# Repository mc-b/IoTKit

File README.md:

Internet der Dinge Kit
----------------------

| IoTKit V1   | IoTKit V2  | IoTKit V3  |
|  :-------:  | :-------:  | :-------:  |
||||
|[Dokumentation](https://github.com/mc-b/IoTKitV1)|[Dokumentation](https://github.com/mc-b/IoTKitV2)|[Dokumentation](https://github.com/mc-b/IoTKitV3)|

### Kurse:

Internet of Things (IoT) 
* [CAS IoT Manager Smarte Lösungen mit Internet of Things (IoT)](https://www.hslu.ch/de-ch/informatik/weiterbildung/networking-and-innovative-technologies/cas-iot/) 
* [Internet of Things (IoT) im Einsatz](https://www.digicomp.ch/weiterbildung/trainings-zu-platforms-services/platform-as-a-service-paas/internet-of-things-iot/internet-of-things-iot-im-einsatz)
* [Für IT- und Software-Architekten](https://www.digicomp.ch/mastering-digital-change/7-kompetenzfelder-fuer-den-digitalen-wandel/handlungsfeld-it/neue-technologien/internet-of-things-iot-fuer-it-und-softwarearchitekten)

Kurse: Technologien und Infrastruktur

* [IoT, Microservices, Machine Learning und DevOps – Moderne Architektur-relevante Methoden und Technologien («MODTEC»)](https://www.digicomp.ch/trends/devops-trainings/iot-microservices-machine-learning-und-devops-moderne-architektur-relevante-methoden-und-technologien)
* [Microservices-Grundlagen («MISEGR»)](https://www.digicomp.ch/weiterbildung/development/software-engineering-trainings/it-architektur/softwarearchitektur/design-organisation/microservices-grundlagen)
* [Docker und Kubernetes – Übersicht und Einsatz («DUK»)](https://www.digicomp.ch/trends/docker-trainings/docker-und-kubernetes-uebersicht-und-einsatz)
* [Machine Learning Grundlagen («MLG»)](https://www.digicomp.ch/weiterbildung/development/iot--ai--vr--machine-learning-training/artificial-intelligence/machine-learning-grundlagen)
* [Software mit agilen Methoden (Scrum) entwickeln](https://www.eb-zuerich.ch/angebot/software-mit-agilen-methoden-scrum-entwickeln.html)
* [Mit Business Process Model and Notation (BPMN) arbeiten](https://www.eb-zuerich.ch/angebot/mit-business-process-model-and-notation-bpmn-arbeiten.html)

### Referate: 

* 12.12.18: [Microservices – Einblick, Umsetzung und zukünftige Entwicklungen («MICREF»)](https://www.digicomp.ch/events/development-events/microservices-einblick-umsetzung-und-zukuenftige-entwicklungen)
* 01.06.18: [Internet of Things trifft Machine Learning, implementiert mittels Microservices](https://informatiktage.ch/veranstaltungen/internet-of-things-trifft-machine-learning/)
* 17.05.17: [IT Infrastruktur "on demand"](https://github.com/mc-b/IoTKit/blob/master/Talks/2017-05-17-IT-Architektur_on_demand.pdf)
* 04.05.17: [Big Data mit Open Source](https://github.com/mc-b/IoTKit/blob/master/Talks/2017-05-04-BigData.pdf)
* 03.05.17: [Vom Umgang mit Containern](https://github.com/mc-b/IoTKit/blob/master/Talks/2017-05-03-VomUmgangmitContainern.pdf)
* 05.04.17: [Internet der Dinge](https://github.com/mc-b/IoTKit/blob/master/Talks/2017-04-05-InternetDerDinge.pdf) 
* 15.03.17: [Big Data und KI](https://github.com/mc-b/IoTKit/blob/master/Talks/2017-03-15-BigDataUndKI.pdf) 
* 01.03.17: [Digital Transformation](https://github.com/mc-b/IoTKit/blob/master/Talks/2017-03-01-DigitaleTransformation.pdf)
* 18.09.16: [Internet of Things – was es ist & wie es Leben rettet](https://github.com/mc-b/IoTKit/blob/master/Talks/2016-09-18-MakerFaire-IoTLebenRetten/MakerFaire_IoTLebenRetten.pdf)
* 18.09.16: [Internet of Things – Anwendung im Alltag am Beispiel Smart Kitchen](https://github.com/mc-b/IoTKit/blob/master/Talks/2016-09-18-MakerFaire-IoTKitchenHelper/MakerFaire_IoTKitchenHelper.pdf)
* 29.08.16: [Industrie 4.0: Wie kommunizieren die Systeme?](https://github.com/mc-b/IoTKit/blob/master/Talks/2016-08-29-NormenStandard/2016-08-29-NormenStandards.pdf)
* 03.06.16: [Internet of Things – was es ist & wie es Leben rettet](https://github.com/mc-b/IoTKit/blob/master/Talks/2016-06-03-IoTLebenRetten/Informatiktage_IoTLebenRetten.pdf)
* 03.06.16: [Internet of Things – Anwendung im Alltag am Beispiel Smart Kitchen](https://github.com/mc-b/IoTKit/blob/master/Talks/2016-06-3-IoTKitchenHelper/Informatiktage_IoTKitchenHelper.pdf)
* 30.03.16: [Spielerisch ins Internet der Dinge](https://github.com/mc-b/IoTKit/blob/master/Talks/2016-03-30-Lernstick/Spielerisch%20ins%20Internet%20der%20Dinge%20-%20USB%20Lernstick-Community-Treffen%20vom%2030.pdf)
* 04.03.16: [Internet der Dinge (IoT) Orchestrierung](https://github.com/mc-b/IoTKit/tree/master/Talks/2016-03-04-IoT_Orchestrierung)
* 04.02.16: [ Infrastructure as Code (Docker, Vagrant und Co. im Einsatz)](http://www.ch-open.ch/fileadmin/user_upload/OBL_ZH_04.02.2016_-_Folien.pdf)
* 02.02.16: [Internet der Dinge (IoT) für Integratoren](http://news.digicomp.ch/de/2016/02/03/opentuesday-slides-internet-der-dinge-iot-fur-integratoren/)
* 13.04.15: [Kommunikation zwischen Applikationen im Internet of Things](https://developer.mbed.org/users/marcel1691/notebook/kommunikation-zwischen-applikationen-im-internet-o/)
* 02.04.15: [Prototype to Product for Internet of Things in One Step](http://www.ch-open.ch/fileadmin/user_upload/events/obl/2015/150402_prototype-to-product-iot.pdf)
* 05.02.15: ["Open" Internet der Dinge (IoT) im Zusammenspiel mit Fachanwendungen und Cloudservices](http://www.ch-open.ch/fileadmin/user_upload/events/obl/2015/20150205_OBL_Internet_der_Dinge.pdf)
* 08.05.14: [FabLab Zürich 2.0](http://www.ch-open.ch/fileadmin/user_upload/events/obl/2014/140508_FabLabVersion2.pdf)
* 06.02.14: [Bottom-up Innovation und Open Source Internet of Things](http://www.ch-open.ch/fileadmin/user_upload/events/obl/2014/140206_OpenSourceIoT.pdf)
* 03.10.13: [Raspberry Pi – erste Erfahrungen und Projekte](http://www.ch-open.ch/fileadmin/user_upload/events/obl/2013/131002_RaspberryPi_Erste_Erfahrungen.pdf)
* 02.05.13: [Internet of Things](http://www.ch-open.ch/fileadmin/user_upload/events/obl/2013/130502_Internet_of_Things.pdf)
* 07.02.13: [FabLab Zürich - Open Software meets Open Hardware](http://www.ch-open.ch/fileadmin/user_upload/events/obl/2013/130207_FabLab_Zuerich_OBL.pdf)
* 03.11.11: [MakerBot as an example of Open Source Hardware](http://www.ch-open.ch/events/obl/obl-2011/)

### Workshops:
- 18.09.2016: [Das Internet der Dinge erlebt die Welt](http://dynamo.ch/kurs/das-internet-der-dinge-erfährt-die-welt) (Zürich Mini Maker Faire)
- 17.09.2016: [Das Internet der Dinge bewegt Roboter](http://dynamo.ch/kurs/das-internet-der-dinge-bewegt-roboter) (Zürich Mini Maker Faire)
- 15.09.2016: [CH Open Workshop - Internet der Dinge](http://www.ch-open.ch/wstage0/workshop-tage/2016/ws-16-internet-der-dinge/)
- 04.06.2016: [Das Internet der Dinge erlebt die Welt](https://informatiktage.ch/veranstaltungen/workshop-iot-sensoren/) (Informatiktage 2016)
- 04.06.2016: [Das Internet der Dinge bewegt Roboter](https://informatiktage.ch/veranstaltungen/iot-roboter/) (Informatiktage 2016)
- 02.09.2015: [/ch/open Workshop](https://developer.mbed.org/teams/ch-open-wstage2015/)
- 28.03.2015: [OSS an Schulen](https://developer.mbed.org/users/marcel1691/notebook/oss-an-schulen/)

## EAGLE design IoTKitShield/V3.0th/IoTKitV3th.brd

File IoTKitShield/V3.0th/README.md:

IoTKit Shield V0.5 - through hole Variante
==========================================

IoTKit Shield basierend auf Arduino Form Faktor. 

Für den Einsatz mit der mbed Plattform (https://developer.mbed.org) und dem
Freescale K64F Board (https://developer.mbed.org/platforms/FRDM-K64F/).

Funktionen
----------
- Sensoren
 * Licht
 * Hall
 * Poti
- Aktoren (bzw. Ansteuerungselemente)
 * Servo
 * DC Motor
 * Schrittmotor
 * LED Strip
- Steckplätze
 * RFID Reader
 * ESP8266 Modem

Reichelt Warenkorb
------------------
https://secure.reichelt.de/index.html?&ACTION=20&AWKID=1029937&PROVID=2084

Lizenz
------
Copyright (C), Marcel mc-b Bernet, Zürich. Alle Unterlagen ist unter der Lizenz „Creative Commons Attribution/Share Alike“ verfügbar.                                       

Haftungsausschluss
------------------
* Bei den Bauanleitungen bzw. irgendwelcher Software gibt es keine Haftung für irgendwelche Schäden oder Funktionsgarantie, bitte immer nur als Anregung auffassen.
* Ich hafte nicht für Schäden, die der Anwender oder Dritte durch die Verwendung der Software oder Hardware verursachen oder erleiden. In keinem Fall hafte ich für entgangenen Umsatz oder Gewinn oder sonstige Vermögensschäden die bei der Verwendung oder durch die Verwendung dieser Programme oder Anleitungen entstehen können.

Weitere Informationen
---------------------
Für eine Ausführliche Einführung empfehle ich die "Internet der Dinge" Kursreihe an der EB Zürich, Schweiz.
* http://kurs.eb-zuerich.ch/is95

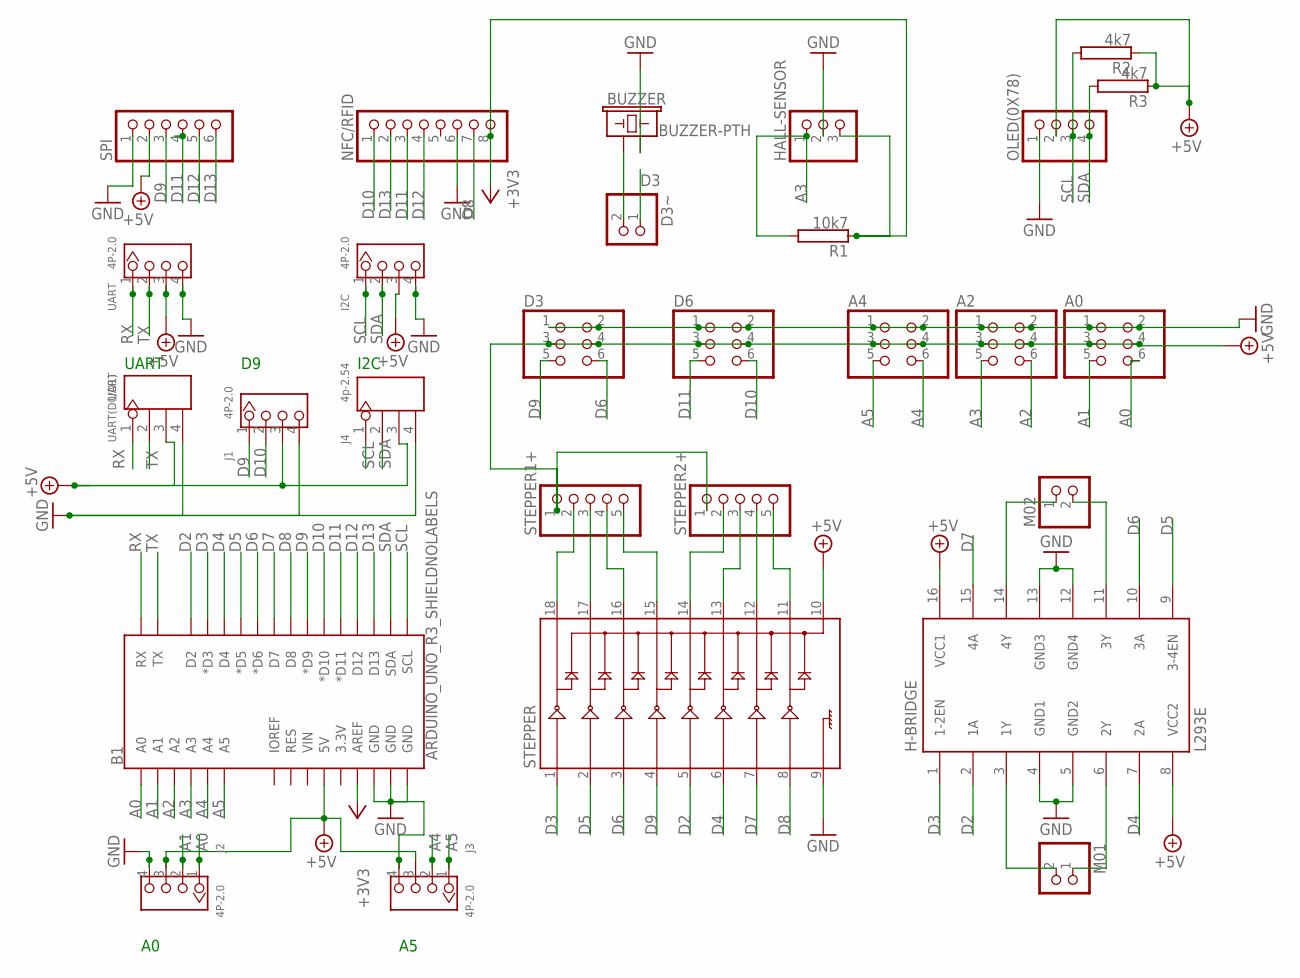
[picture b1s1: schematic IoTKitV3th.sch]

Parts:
A0, A2, A4: PINHD-2X3; 2X03
B1: ARDUINO_UNO_R3_SHIELDNOLABELS; UNO_R3_SHIELD_NOLABELS
BUZZER: BUZZER-PTH; BUZZER-12MM
D3, D6: PINHD-2X3; 2X03
D3~: PINHD-1X2; 1X02
H-BRIDGE: L293E; DIL16
HALL-SENSOR: PINHD-1X3; 1X03
I2C: 4P-2.0; HW4-2.0
J1, J2, J3: 4P-2.0; HW4-2.0
J4: 4p-2.54; H4-2.54
M01, M02: PINHD-1X2; 1X02
NFC/RFID: PINHD-1X8; 1X08
OLED(0X78): PINHD-1X4; 1X04
R1: 10k7; CA0001
R2, R3: 4k7; CA0001
SPI: PINHD-1X6; 1X06
STEPPER: ULN2803DIP; DIL18
STEPPER1+, STEPPER2+: PINHD-1X5; 1X05
UART: 4P-2.0; HW4-2.0
UART(D0/D1): UART; H4-2.54

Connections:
+3V3: B1.AREF, HALL-SENSOR.3, NFC/RFID.8, R1.1
+5V: A0.3, A0.4, A2.3, A2.4, A4.3, A4.4, B1.5V, D3.3, D3.4, D6.3, D6.4, H-BRIDGE.8 (VCC2), H-BRIDGE.16 (VCC1), I2C.3, J1.3, J2.3, J3.3, J4.3, OLED(0X78).2, R2.1, R3.1, SPI.2, STEPPER.10, STEPPER1+.1, STEPPER2+.1, UART.3, UART(D0/D1).3
A0: A0.6, B1.A0, J2.1
A1: A0.5, B1.A1, J2.2
A2: A2.6, B1.A2
A3: A2.5, B1.A3, HALL-SENSOR.1, R1.2
A4: A4.6, B1.A4, J3.2
A5: A4.5, B1.A5, J3.1
D2: B1.D2, H-BRIDGE.2 (1A), STEPPER.5
D3: B1.D3 (*D3), D3~.1, H-BRIDGE.1 (1-2EN), STEPPER.1
D4: B1.D4, H-BRIDGE.7 (2A), STEPPER.6
D5: B1.D5 (*D5), H-BRIDGE.9 (3-4EN), STEPPER.2
D6: B1.D6 (*D6), D3.6, H-BRIDGE.10 (3A), STEPPER.3
D7: B1.D7, H-BRIDGE.15 (4A), STEPPER.7
D8: B1.D8, NFC/RFID.7, STEPPER.8
D9: B1.D9 (*D9), D3.5, J1.1, SPI.3, STEPPER.4
D10: B1.D10 (*D10), D6.6, J1.2, NFC/RFID.1
D11: B1.D11 (*D11), D6.5, NFC/RFID.3, SPI.4
D12: B1.D12, NFC/RFID.4, SPI.5
D13: B1.D13, NFC/RFID.2, SPI.6
GND: A0.1, A0.2, A2.1, A2.2, A4.1, A4.2, B1.GND@0 (GND), B1.GND@1 (GND), B1.GND@2 (GND), BUZZER.- (2), D3.1, D3.2, D6.1, D6.2, H-BRIDGE.4 (GND1), H-BRIDGE.5 (GND2), H-BRIDGE.12 (GND4), H-BRIDGE.13 (GND3), HALL-SENSOR.2, I2C.4, J1.4, J2.4, J3.4, J4.4, NFC/RFID.6, OLED(0X78).1, SPI.1, STEPPER.9, UART.4, UART(D0/D1).4
M01: H-BRIDGE.6 (2Y), M01.1
unnamed: STEPPER.14, STEPPER2+.2
unnamed: STEPPER.13, STEPPER2+.3
unnamed: STEPPER.12, STEPPER2+.4
unnamed: STEPPER.11, STEPPER2+.5
unnamed: BUZZER.+ (1), D3~.2
unnamed: STEPPER.18, STEPPER1+.2
unnamed: STEPPER.17, STEPPER1+.3
unnamed: STEPPER.16, STEPPER1+.4
unnamed: STEPPER.15, STEPPER1+.5
unnamed: H-BRIDGE.14 (4Y), M02.1
unnamed: H-BRIDGE.11 (3Y), M02.2
unnamed: H-BRIDGE.3 (1Y), M01.2
RX: B1.RX, UART.1, UART(D0/D1).1
SCL: B1.SCL, I2C.1, J4.1, OLED(0X78).3, R2.2
SDA: B1.SDA, I2C.2, J4.2, OLED(0X78).4, R3.2
TX: B1.TX, UART.2, UART(D0/D1).2

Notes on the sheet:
UART
I2C

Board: 2 copper layers, 28 parts (0 on the bottom side), 38 nets, no tracks yet.

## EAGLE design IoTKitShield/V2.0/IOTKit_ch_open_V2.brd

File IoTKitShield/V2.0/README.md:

IoTKit Shield V2.0 - SMD Variante
==========================================

IoTKit Shield basierend auf Arduino Form Faktor. 

Für den Einsatz mit der mbed Plattform (https://developer.mbed.org) und dem
Freescale K64F Board (https://developer.mbed.org/platforms/FRDM-K64F/).

Funktionen
----------
- Sensoren
 * Licht
 * Hall
 * Poti
- Aktoren (bzw. Ansteuerungselemente)
 * Servo
 * DC Motor
 * Schrittmotor
 * LED Strip
- Steckplätze
 * RFID Reader
 * ESP8266 Modem

Weitere Informationen
---------------------
Für eine Ausführliche Einführung empfehle ich die "Internet der Dinge" Kursreihe an der EB Zürich, Schweiz.
* http://kurs.eb-zuerich.ch/is95

Lizenz
------
Copyright (C), Marcel mc-b Bernet, Zürich. Alle Unterlagen ist unter der Lizenz „Creative Commons Attribution/Share Alike“ verfügbar.                                       

Haftungsausschluss
------------------
* Bei den Bauanleitungen bzw. irgendwelcher Software gibt es keine Haftung für irgendwelche Schäden oder Funktionsgarantie, bitte immer nur als Anregung auffassen.
* Ich hafte nicht für Schäden, die der Anwender oder Dritte durch die Verwendung der Software oder Hardware verursachen oder erleiden. In keinem Fall hafte ich für entgangenen Umsatz oder Gewinn oder sonstige Vermögensschäden die bei der Verwendung oder durch die Verwendung dieser Programme oder Anleitungen entstehen können.

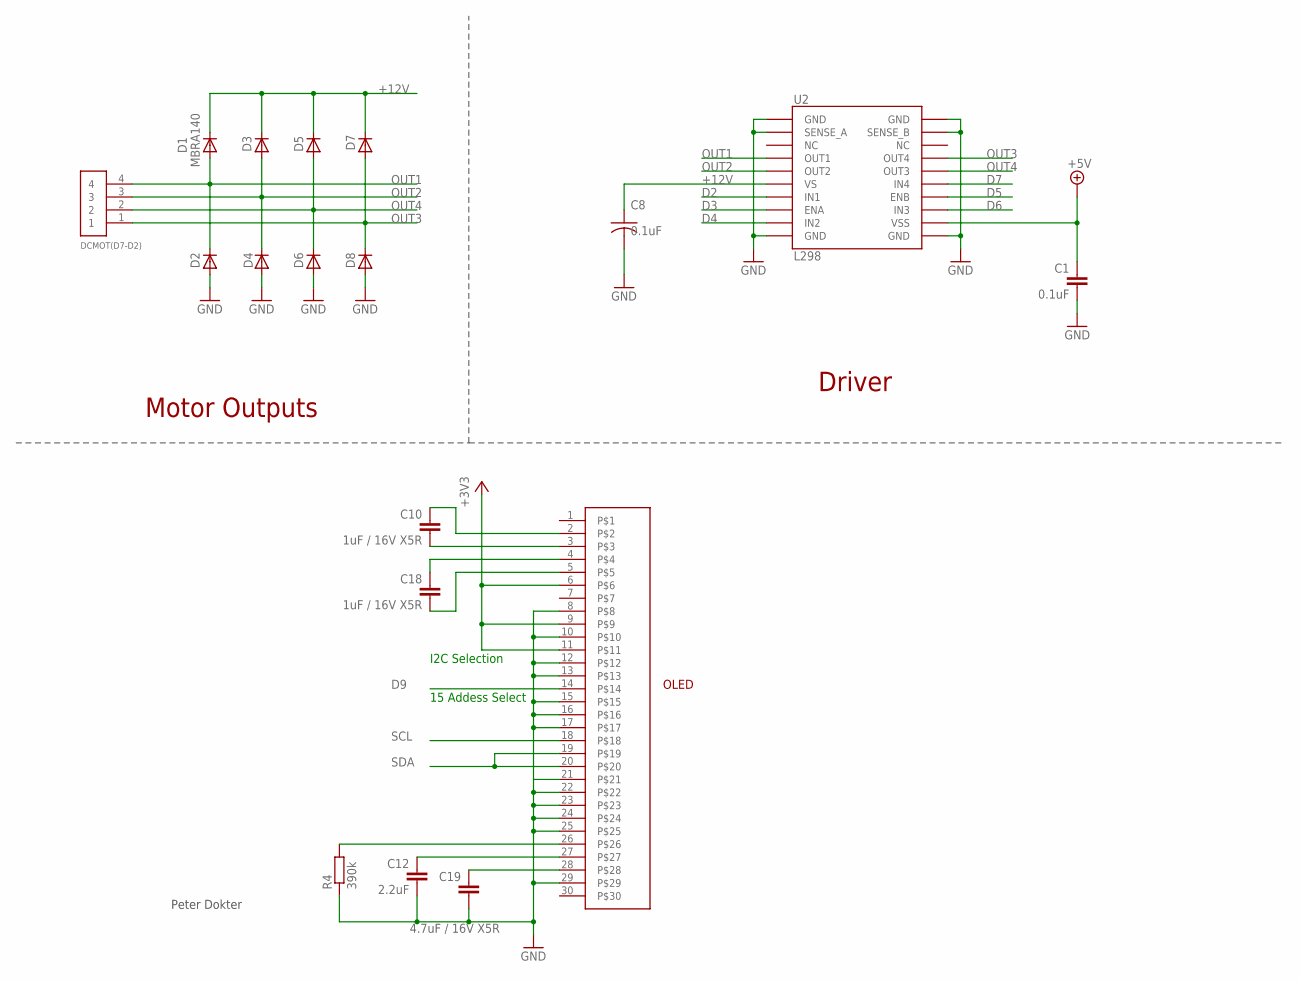
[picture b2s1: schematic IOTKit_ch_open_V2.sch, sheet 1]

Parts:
C1: 0.1uF; 0402-CAP
C8: 0.1uF; C0603K
C10, C18: 1uF / 16V X5R; 0603-CAP
C12: 2.2uF; 0603-CAP
C19: 4.7uF / 16V X5R; 0603-CAP
D1, D2, D3, D4, D5, D6, D7, D8: MBRA140; SMA-DIODE
DCMOT(D7-D2): 1X4; 1X04_LINE
R4: 390k; R0603
U2: L298; POWERSO20
U$4: OLED_096_1

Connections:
+3V3: U$4.6, U$4.9, U$4.11; also elsewhere on the board
+5V: C1.1, U2.P$12 (VSS); also elsewhere on the board
+12V: C8.1, D1.C, D3.C, D5.C, D7.C, U2.P$6 (VS); also elsewhere on the board
D2: U2.P$7 (IN1); also elsewhere on the board
D3: U2.P$8 (ENA); also elsewhere on the board
D4: U2.P$9 (IN2); also elsewhere on the board
D5: U2.P$14 (ENB); also elsewhere on the board
D6: U2.P$13 (IN3); also elsewhere on the board
D7: U2.P$15 (IN4); also elsewhere on the board
D9: U$4.14; also elsewhere on the board
GND: C1.2, C8.2, C12.2, C19.2, D2.A, D4.A, D6.A, D8.A, R4.1, U2.P$1 (GND), U2.P$2 (SENSE_A), U2.P$10 (GND), U2.P$11 (GND), U2.P$19 (SENSE_B), U2.P$20 (GND), U$4.8, U$4.10, U$4.12, U$4.13, U$4.15, U$4.16, U$4.17, U$4.21, U$4.22, U$4.23, U$4.24, U$4.25, U$4.29; also elsewhere on the board
unnamed: C18.2, U$4.5
unnamed: R4.2, U$4.26
unnamed: C19.1, U$4.28
unnamed: C12.1, U$4.27
unnamed: C18.1, U$4.4
unnamed: C10.2, U$4.3
unnamed: C10.1, U$4.2
OUT1: D1.A, D2.C, DCMOT(D7-D2).4, U2.P$4 (OUT1)
OUT2: D3.A, D4.C, DCMOT(D7-D2).3, U2.P$5 (OUT2)
OUT3: D7.A, D8.C, DCMOT(D7-D2).1, U2.P$17 (OUT4)
OUT4: D5.A, D6.C, DCMOT(D7-D2).2, U2.P$16 (OUT3)
SCL: U$4.18; also elsewhere on the board
SDA: U$4.19, U$4.20; also elsewhere on the board

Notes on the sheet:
Motor Outputs
Driver
Peter Dokter
I2C Selection
15 Addess Select

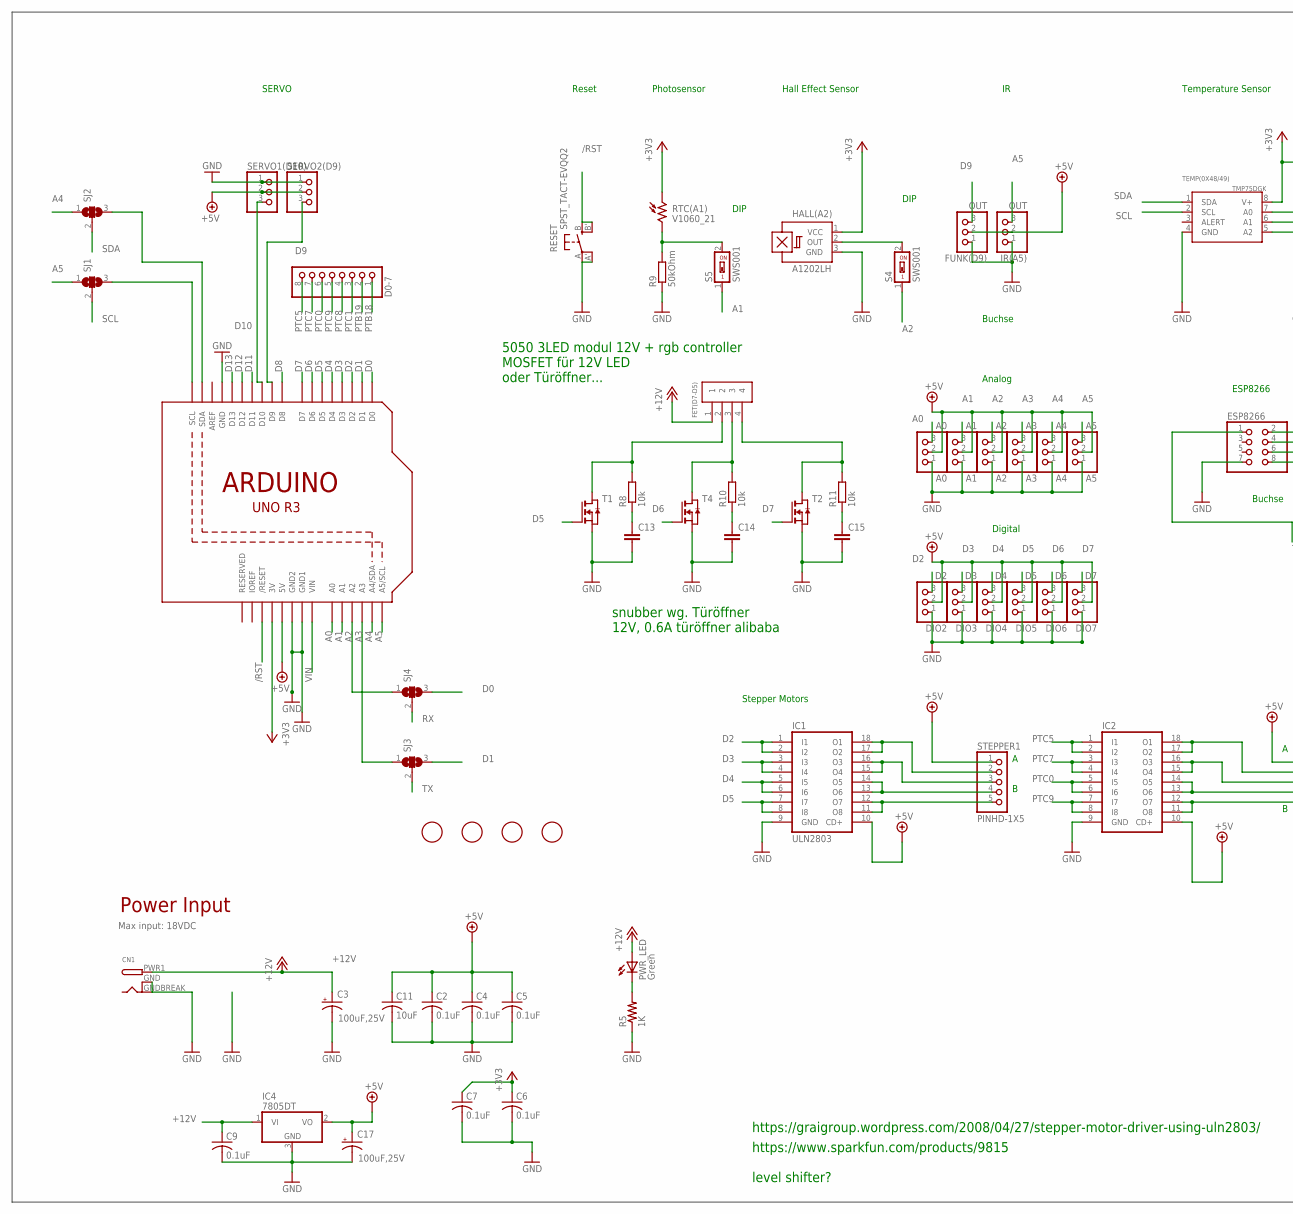
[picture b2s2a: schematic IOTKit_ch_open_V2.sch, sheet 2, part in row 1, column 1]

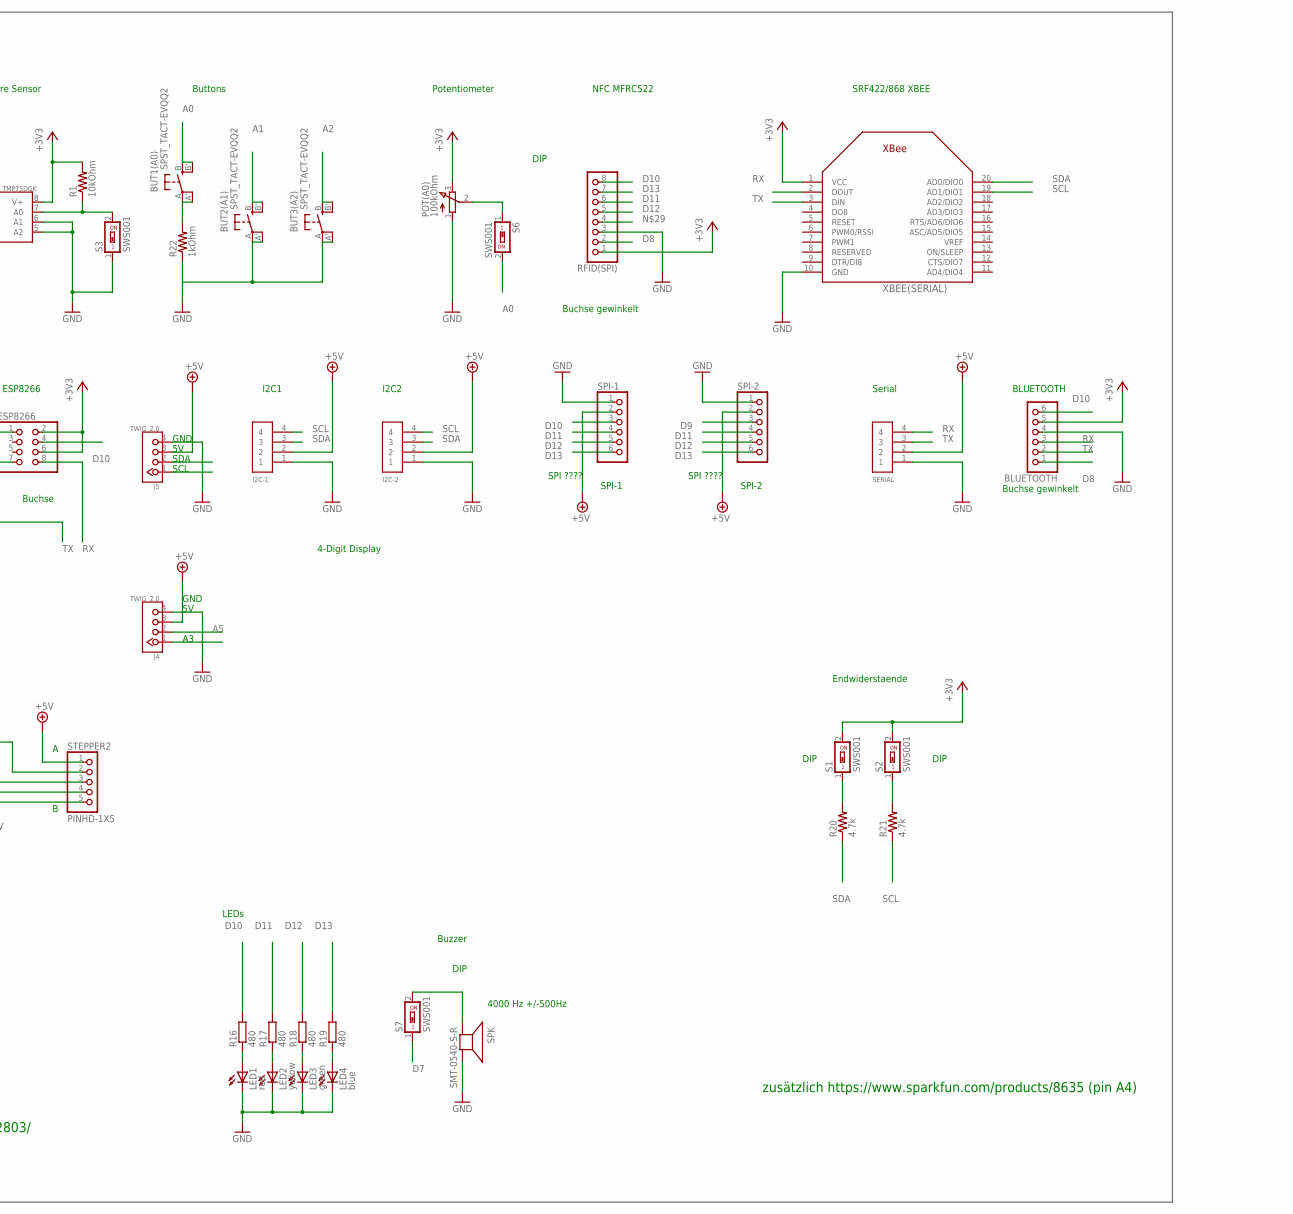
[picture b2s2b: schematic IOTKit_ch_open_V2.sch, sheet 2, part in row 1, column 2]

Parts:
A0: A0; 1X03_LINE
A1: A1; 1X03_LINE
A2: A2; 1X03_LINE
A3: A3; 1X03_LINE
A4: A4; 1X03_LINE
A5: A5; 1X03_LINE
BLUETOOTH: PINHD-1X6B; 1X06-BIG
BUT1(A0), BUT2(A1), BUT3(A2): SPST_TACT-EVQQ2; EVQ-Q2
C2, C4, C5, C6, C7: 0.1uF; C0603K
C3, C17: 100uF,25V; NIPPON_F80
C9: 0.1uF; C0805K
C11: 10uF; C0805K
C13, C14, C15: C-EUC0603; C0603
CN1: DCBARRELSMT; DCJACK_2MM_SMT
D0-7: PINHD-1X8CLEANBIG; 1X08-CLEANBIG
DIO2: D2; 1X03_LINE
DIO3: D3; 1X03_LINE
DIO4: D4; 1X03_LINE
DIO5: D5; 1X03_LINE
DIO6: D6; 1X03_LINE
DIO7: D7; 1X03_LINE
ESP8266: PINHD-2X4; 2X04
FET(D7-D5): 1X4; 1X04_LINE
FUNK(D9): OUT; 1X03_LINE
HALL(A2): A1202LH; SOT23-W
I2C-1, I2C-2: 1X4; 1X04_LINE
IC1: ULN2803; SO18W
IC2: ULN2803ASO18W; SO18W
IC4: 7805DT; TO252
IR(A5): OUT; 1X03_LINE
J4, J5: TWIG_2.0; 2.0_1X4
LED1: red; CHIP-LED0603
LED2: yellow; CHIP-LED0603
LED3: green; CHIP-LED0603
LED4: blue; CHIP-LED0603
POT(A0): 100kOhm; EVUF
PWR_LED: Green; CHIP-LED0805
R1: 10kOhm; R0805
R5: 1K; R0805
R8, R10, R11: 10k; R0805
R9: 50kOhm; R0603
R16, R17, R18, R19: 480; R0603
R20, R21: 4.7k; R0805
R22: 1kOhm; R0805
RESET: SPST_TACT-EVQQ2; EVQ-Q2
RFID(SPI): PINHD-1X8BIG; 1X08-BIG
RTC(A1): V1060_21; TO-5_V10
S1, S2, S3, S4, S5, S6, S7: SWS001; SMS-001
SERIAL: 1X4; 1X04_LINE
SERVO1(D10), SERVO2(D9): PINHD-1X3; 1X03
SJ1, SJ2, SJ3, SJ4: SJ2W; SJ_2
SPI-1, SPI-2: PINHD-1X6B; 1X06-BIG
SPK: SMT-0540-S-R
STEPPER1, STEPPER2: PINHD-1X5; 1X05
T1, T2, T4: NMOSSOT223; SOT223
TEMP(0X48/49): TMP75DGK; MSOP8
U$1, U$2, U$3, U$6: FIDUCIAL; FIDUCIAL_1MM
U$5: ARDUINOR3NONAME; ARDUINOR2_ICSP_NODIM_NONAME
XBEE(SERIAL): XBEE

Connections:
+3V3: BLUETOOTH.5, C6.1, C7.1, ESP8266.2, ESP8266.6, HALL(A2).1 (VCC), POT(A0).3 (E), R1.2, RFID(SPI).1, RTC(A1).1, S1.2, S2.2, TEMP(0X48/49).8 (V+), U$5.3V, XBEE(SERIAL).1 (VCC); also elsewhere on the board
+5V: A0.2, A1.2, A2.2, A3.2, A4.2, A5.2, C2.1, C4.1, C5.1, C11.1, C17.+, DIO2.2, DIO3.2, DIO4.2, DIO5.2, DIO6.2, DIO7.2, FUNK(D9).2, I2C-1.2, I2C-2.2, IC1.10 (CD+), IC2.10 (CD+), IC4.2 (VO), IR(A5).2, J4.3, J5.3, SERIAL.2, SERVO1(D10).2, SERVO2(D9).2, SPI-1.2, SPI-2.2, STEPPER1.1, STEPPER2.1, U$5.5V; also elsewhere on the board
+12V: C3.+, C9.1, CN1.PWR1 (PWR), FET(D7-D5).1, IC4.1 (VI), PWR_LED.A; also elsewhere on the board
/RST: RESET.B (S), RESET.B' (S1), U$5.RESET (/RESET)
A0: A0.3, BUT1(A0).B (S), BUT1(A0).B' (S1), S6.2, U$5.A0
A1: A1.3, BUT2(A1).B (S), BUT2(A1).B' (S1), S5.1, U$5.A1
A2: A2.3, BUT3(A2).B (S), BUT3(A2).B' (S1), S4.1, SJ4.1, U$5.A2
A3: A3.3, J4.1, SJ3.1, U$5.A3
A4: A4.3, SJ2.1, U$5.A4 (A4/SDA)
A5: A5.3, IR(A5).3, J4.2, SJ1.1, U$5.A5 (A5/SCL)
D0: SJ4.3, U$5.D0
D1: SJ3.3, U$5.D1
D2: DIO2.3, IC1.1 (I1), IC1.2 (I2), U$5.D2; also elsewhere on the board
D3: DIO3.3, IC1.3 (I3), IC1.4 (I4), U$5.D3; also elsewhere on the board
D4: DIO4.3, IC1.5 (I5), IC1.6 (I6), U$5.D4; also elsewhere on the board
D5: DIO5.3, IC1.7 (I7), IC1.8 (I8), T1.1 (G), U$5.D5; also elsewhere on the board
D6: DIO6.3, T4.1 (G), U$5.D6; also elsewhere on the board
D7: DIO7.3, S7.1, T2.1 (G), U$5.D7; also elsewhere on the board
D8: BLUETOOTH.1, RFID(SPI).2, U$5.D8
D9: FUNK(D9).3, SERVO2(D9).3, SPI-2.3, U$5.D9; also elsewhere on the board
D10: BLUETOOTH.6, ESP8266.4, R16.2, RFID(SPI).8, SERVO1(D10).3, SPI-1.3, U$5.D10
D11: R17.2, RFID(SPI).6, SPI-1.4, SPI-2.4, U$5.D11
D12: R18.2, RFID(SPI).5, SPI-1.5, SPI-2.5, U$5.D12
D13: R19.2, RFID(SPI).7, SPI-1.6, SPI-2.6, U$5.D13
GND: A0.1, A1.1, A2.1, A3.1, A4.1, A5.1, BLUETOOTH.4, BUT2(A1).A, BUT2(A1).A' (P1), BUT3(A2).A, BUT3(A2).A' (P1), C2.2, C3.-, C4.2, C5.2, C6.2, C7.2, C9.2, C11.2, C13.2, C14.2, C15.2, C17.-, CN1.GND (GNDBREAK), CN1.GNDBREAK (GND), DIO2.1, DIO3.1, DIO4.1, DIO5.1, DIO6.1, DIO7.1, ESP8266.7, FUNK(D9).1, HALL(A2).3 (GND), I2C-1.1, I2C-2.1, IC1.9 (GND), IC2.9 (GND), IC4.3 (GND), IR(A5).1, J4.4, J5.4, LED1.C, LED2.C, LED3.C, LED4.C, POT(A0).1 (A), R5.1, R9.1, R22.1, RESET.A, RESET.A' (P1), RFID(SPI).3, S3.1, SERIAL.1, SERVO1(D10).1, SERVO2(D9).1, SPI-1.1, SPI-2.1, SPK.+ (-), T1.3 (S), T2.3 (S), T4.3 (S), TEMP(0X48/49).4 (GND), TEMP(0X48/49).5 (A2), TEMP(0X48/49).6 (A1), U$5.GND, U$5.GND@1 (GND1), U$5.GND@2 (GND2), XBEE(SERIAL).10 (GND); also elsewhere on the board
unnamed: R20.2, S1.1
unnamed: R9.2, RTC(A1).2, S5.2
unnamed: HALL(A2).2 (OUT), S4.2
unnamed: R21.2, S2.1
unnamed: POT(A0).2 (S), S6.1
unnamed: S7.2, SPK.- (+)
unnamed: R1.1, S3.2, TEMP(0X48/49).7 (A0)
unnamed: SJ1.3, U$5.SCL
unnamed: SJ2.3, U$5.SDA
unnamed: LED1.A, R16.1
unnamed: LED2.A, R17.1
unnamed: LED3.A, R18.1
unnamed: LED4.A, R19.1
unnamed: IC2.11 (O8), IC2.12 (O7), STEPPER2.5
unnamed: IC2.13 (O6), IC2.14 (O5), STEPPER2.4
unnamed: IC2.15 (O4), IC2.16 (O3), STEPPER2.3
unnamed: IC2.17 (O2), IC2.18 (O1), STEPPER2.2
unnamed: BUT1(A0).A, BUT1(A0).A' (P1), R22.2
unnamed: C13.1, R8.1
unnamed: FET(D7-D5).2, R8.2, T1.2 (D), T1.4 (D)
unnamed: C14.1, R10.1
unnamed: FET(D7-D5).3, R10.2, T4.2 (D), T4.4 (D)
unnamed: C15.1, R11.1
unnamed: FET(D7-D5).4, R11.2, T2.2 (D), T2.4 (D)
unnamed: IC1.11 (O8), IC1.12 (O7), STEPPER1.5
unnamed: IC1.13 (O6), IC1.14 (O5), STEPPER1.4
unnamed: IC1.15 (O4), IC1.16 (O3), STEPPER1.3
unnamed: IC1.17 (O2), IC1.18 (O1), STEPPER1.2
PTB18: D0-7.1
PTB19: D0-7.2
PTC0: D0-7.6, IC2.5 (I5), IC2.6 (I6)
PTC1: D0-7.3
PTC5: D0-7.8, IC2.1 (I1), IC2.2 (I2)
PTC7: D0-7.7, IC2.3 (I3), IC2.4 (I4)
PTC8: D0-7.4
PTC9: D0-7.5, IC2.7 (I7), IC2.8 (I8)
PWR_LED: PWR_LED.C, R5.2
RX: BLUETOOTH.3, ESP8266.8, SERIAL.4, SJ4.2, XBEE(SERIAL).2 (DOUT)
SCL: I2C-1.4, I2C-2.4, J5.1, R21.1, SJ1.2, TEMP(0X48/49).2 (SCL), XBEE(SERIAL).19 (AD1/DIO1); also elsewhere on the board
SDA: I2C-1.3, I2C-2.3, J5.2, R20.1, SJ2.2, TEMP(0X48/49).1 (SDA), XBEE(SERIAL).20 (AD0/DIO0); also elsewhere on the board
TX: BLUETOOTH.2, ESP8266.1, SERIAL.3, SJ3.2, XBEE(SERIAL).3 (DIN)
VIN: U$5.VIN

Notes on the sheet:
ESP8266
Analog
Temperature Sensor
Buttons
Hall Effect Sensor
Reset
Photosensor
Potentiometer
I2C1
I2C2
Serial
SPI-1
SPI-2
SPI ????
Digital
4-Digit Display
Buzzer
4000 Hz +/-500Hz
LEDs
NFC MFRC522
SRF422/868 XBEE
https://www.sparkfun.com/products/9815
level shifter?
https://graigroup.wordpress.com/2008/04/27/stepper-motor-driver-using-uln2803/
MOSFET für 12V LED oder Türöffner...
5050 3LED modul 12V + rgb controller
snubber wg. Türöffner 12V, 0.6A türöffner alibaba
zusätzlich https://www.sparkfun.com/products/8635 (pin A4)
Stepper Motors
Power Input
Max input: 18VDC
Buchse
Buchse gewinkelt
SERVO
Endwiderstaende
BLUETOOTH
DIP
GND
SDA
SCL

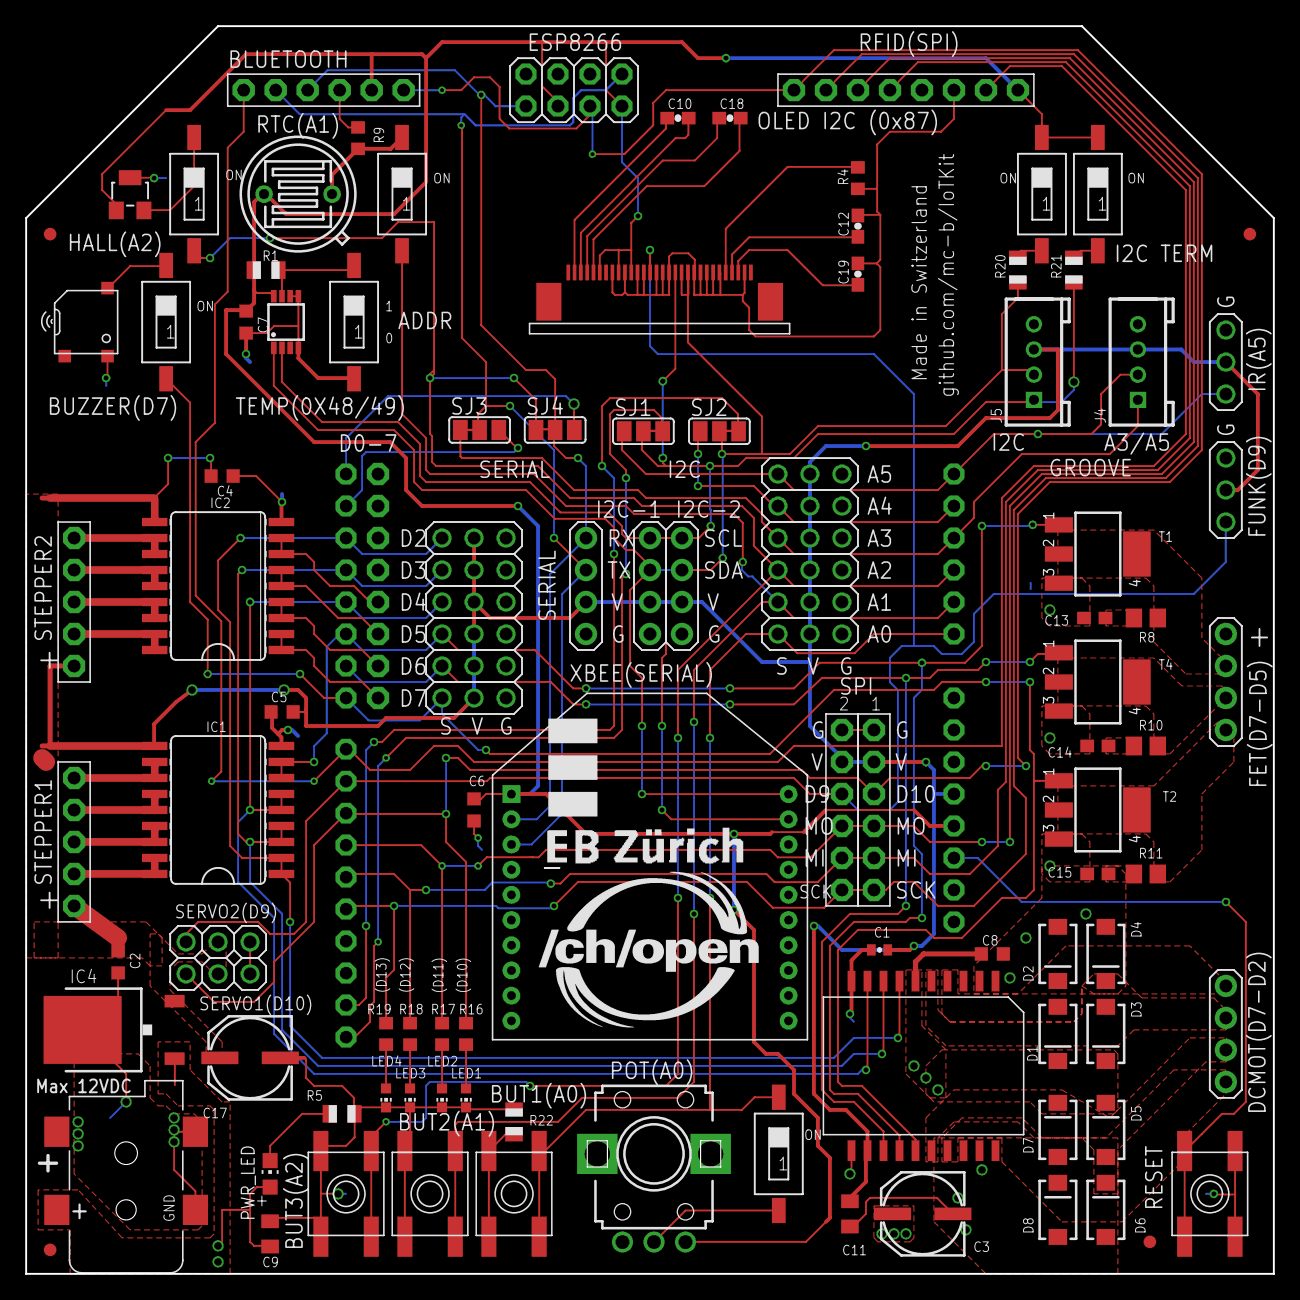
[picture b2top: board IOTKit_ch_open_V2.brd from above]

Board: 2 copper layers, 99.1 x 99.1 mm, 111 parts (0 on the bottom side), 73 nets.

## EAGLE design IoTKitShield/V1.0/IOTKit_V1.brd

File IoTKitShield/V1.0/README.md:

IoTKit Shield V1.0 - SMD Variante
==========================================

IoTKit Shield basierend auf Arduino Form Faktor. 

Für den Einsatz mit der mbed Plattform (https://developer.mbed.org) und dem
Freescale K64F Board (https://developer.mbed.org/platforms/FRDM-K64F/).

Beschreibung und Funktionen
---------------------------
* https://developer.mbed.org/users/marcel1691/notebook/internet-of-things-kit-iotkit-smd-shield/

Weitere Informationen
---------------------
Für eine Ausführliche Einführung empfehle ich die "Internet der Dinge" Kursreihe an der EB Zürich, Schweiz.
* http://kurs.eb-zuerich.ch/is95

Lizenz
------
Copyright (C), Marcel mc-b Bernet, Zürich. Alle Unterlagen ist unter der Lizenz „Creative Commons Attribution/Share Alike“ verfügbar.                                       

Haftungsausschluss
------------------
* Bei den Bauanleitungen bzw. irgendwelcher Software gibt es keine Haftung für irgendwelche Schäden oder Funktionsgarantie, bitte immer nur als Anregung auffassen.
* Ich hafte nicht für Schäden, die der Anwender oder Dritte durch die Verwendung der Software oder Hardware verursachen oder erleiden. In keinem Fall hafte ich für entgangenen Umsatz oder Gewinn oder sonstige Vermögensschäden die bei der Verwendung oder durch die Verwendung dieser Programme oder Anleitungen entstehen können.

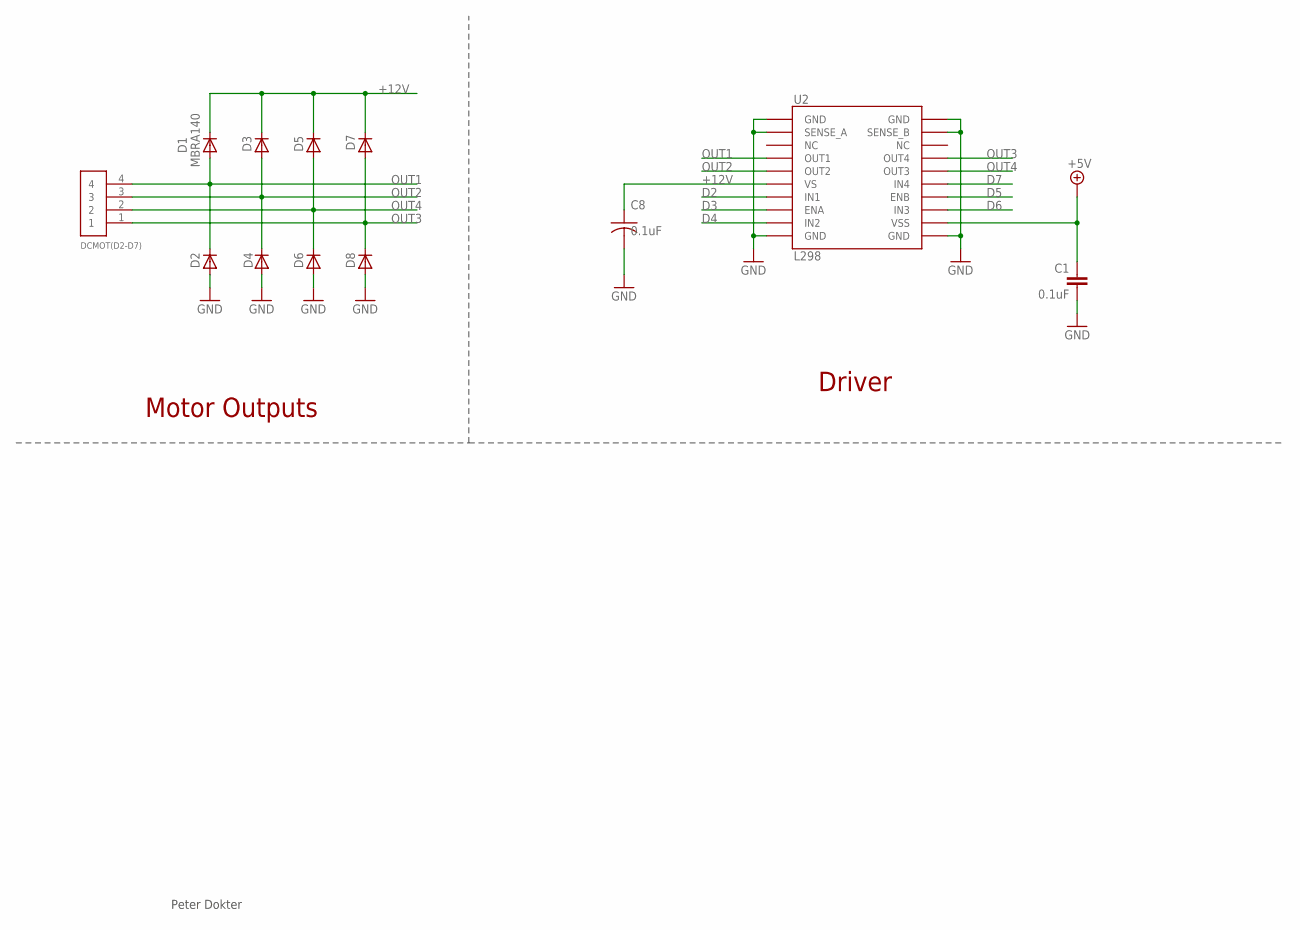
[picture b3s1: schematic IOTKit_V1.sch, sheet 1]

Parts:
C1: 0.1uF; 0402-CAP
C8: 0.1uF; C0603K
D1, D2, D3, D4, D5, D6, D7, D8: MBRA140; SMA-DIODE
DCMOT(D2-D7): 1X4; 1X04_LINE
U2: L298; POWERSO20

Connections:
+5V: C1.1, U2.P$12 (VSS); also elsewhere on the board
+12V: C8.1, D1.C, D3.C, D5.C, D7.C, U2.P$6 (VS); also elsewhere on the board
D2: U2.P$7 (IN1); also elsewhere on the board
D3: U2.P$8 (ENA); also elsewhere on the board
D4: U2.P$9 (IN2); also elsewhere on the board
D5: U2.P$14 (ENB); also elsewhere on the board
D6: U2.P$13 (IN3); also elsewhere on the board
D7: U2.P$15 (IN4); also elsewhere on the board
GND: C1.2, C8.2, D2.A, D4.A, D6.A, D8.A, U2.P$1 (GND), U2.P$2 (SENSE_A), U2.P$10 (GND), U2.P$11 (GND), U2.P$19 (SENSE_B), U2.P$20 (GND); also elsewhere on the board
OUT1: D1.A, D2.C, DCMOT(D2-D7).4, U2.P$4 (OUT1)
OUT2: D3.A, D4.C, DCMOT(D2-D7).3, U2.P$5 (OUT2)
OUT3: D7.A, D8.C, DCMOT(D2-D7).1, U2.P$17 (OUT4)
OUT4: D5.A, D6.C, DCMOT(D2-D7).2, U2.P$16 (OUT3)

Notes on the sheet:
Motor Outputs
Driver
Peter Dokter

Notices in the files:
parts and their libraries:
SparkFun-Boards: Licensing: Creative Commons ShareAlike 4.0 International - https://creativecommons.org/licenses/by-sa/4.0
